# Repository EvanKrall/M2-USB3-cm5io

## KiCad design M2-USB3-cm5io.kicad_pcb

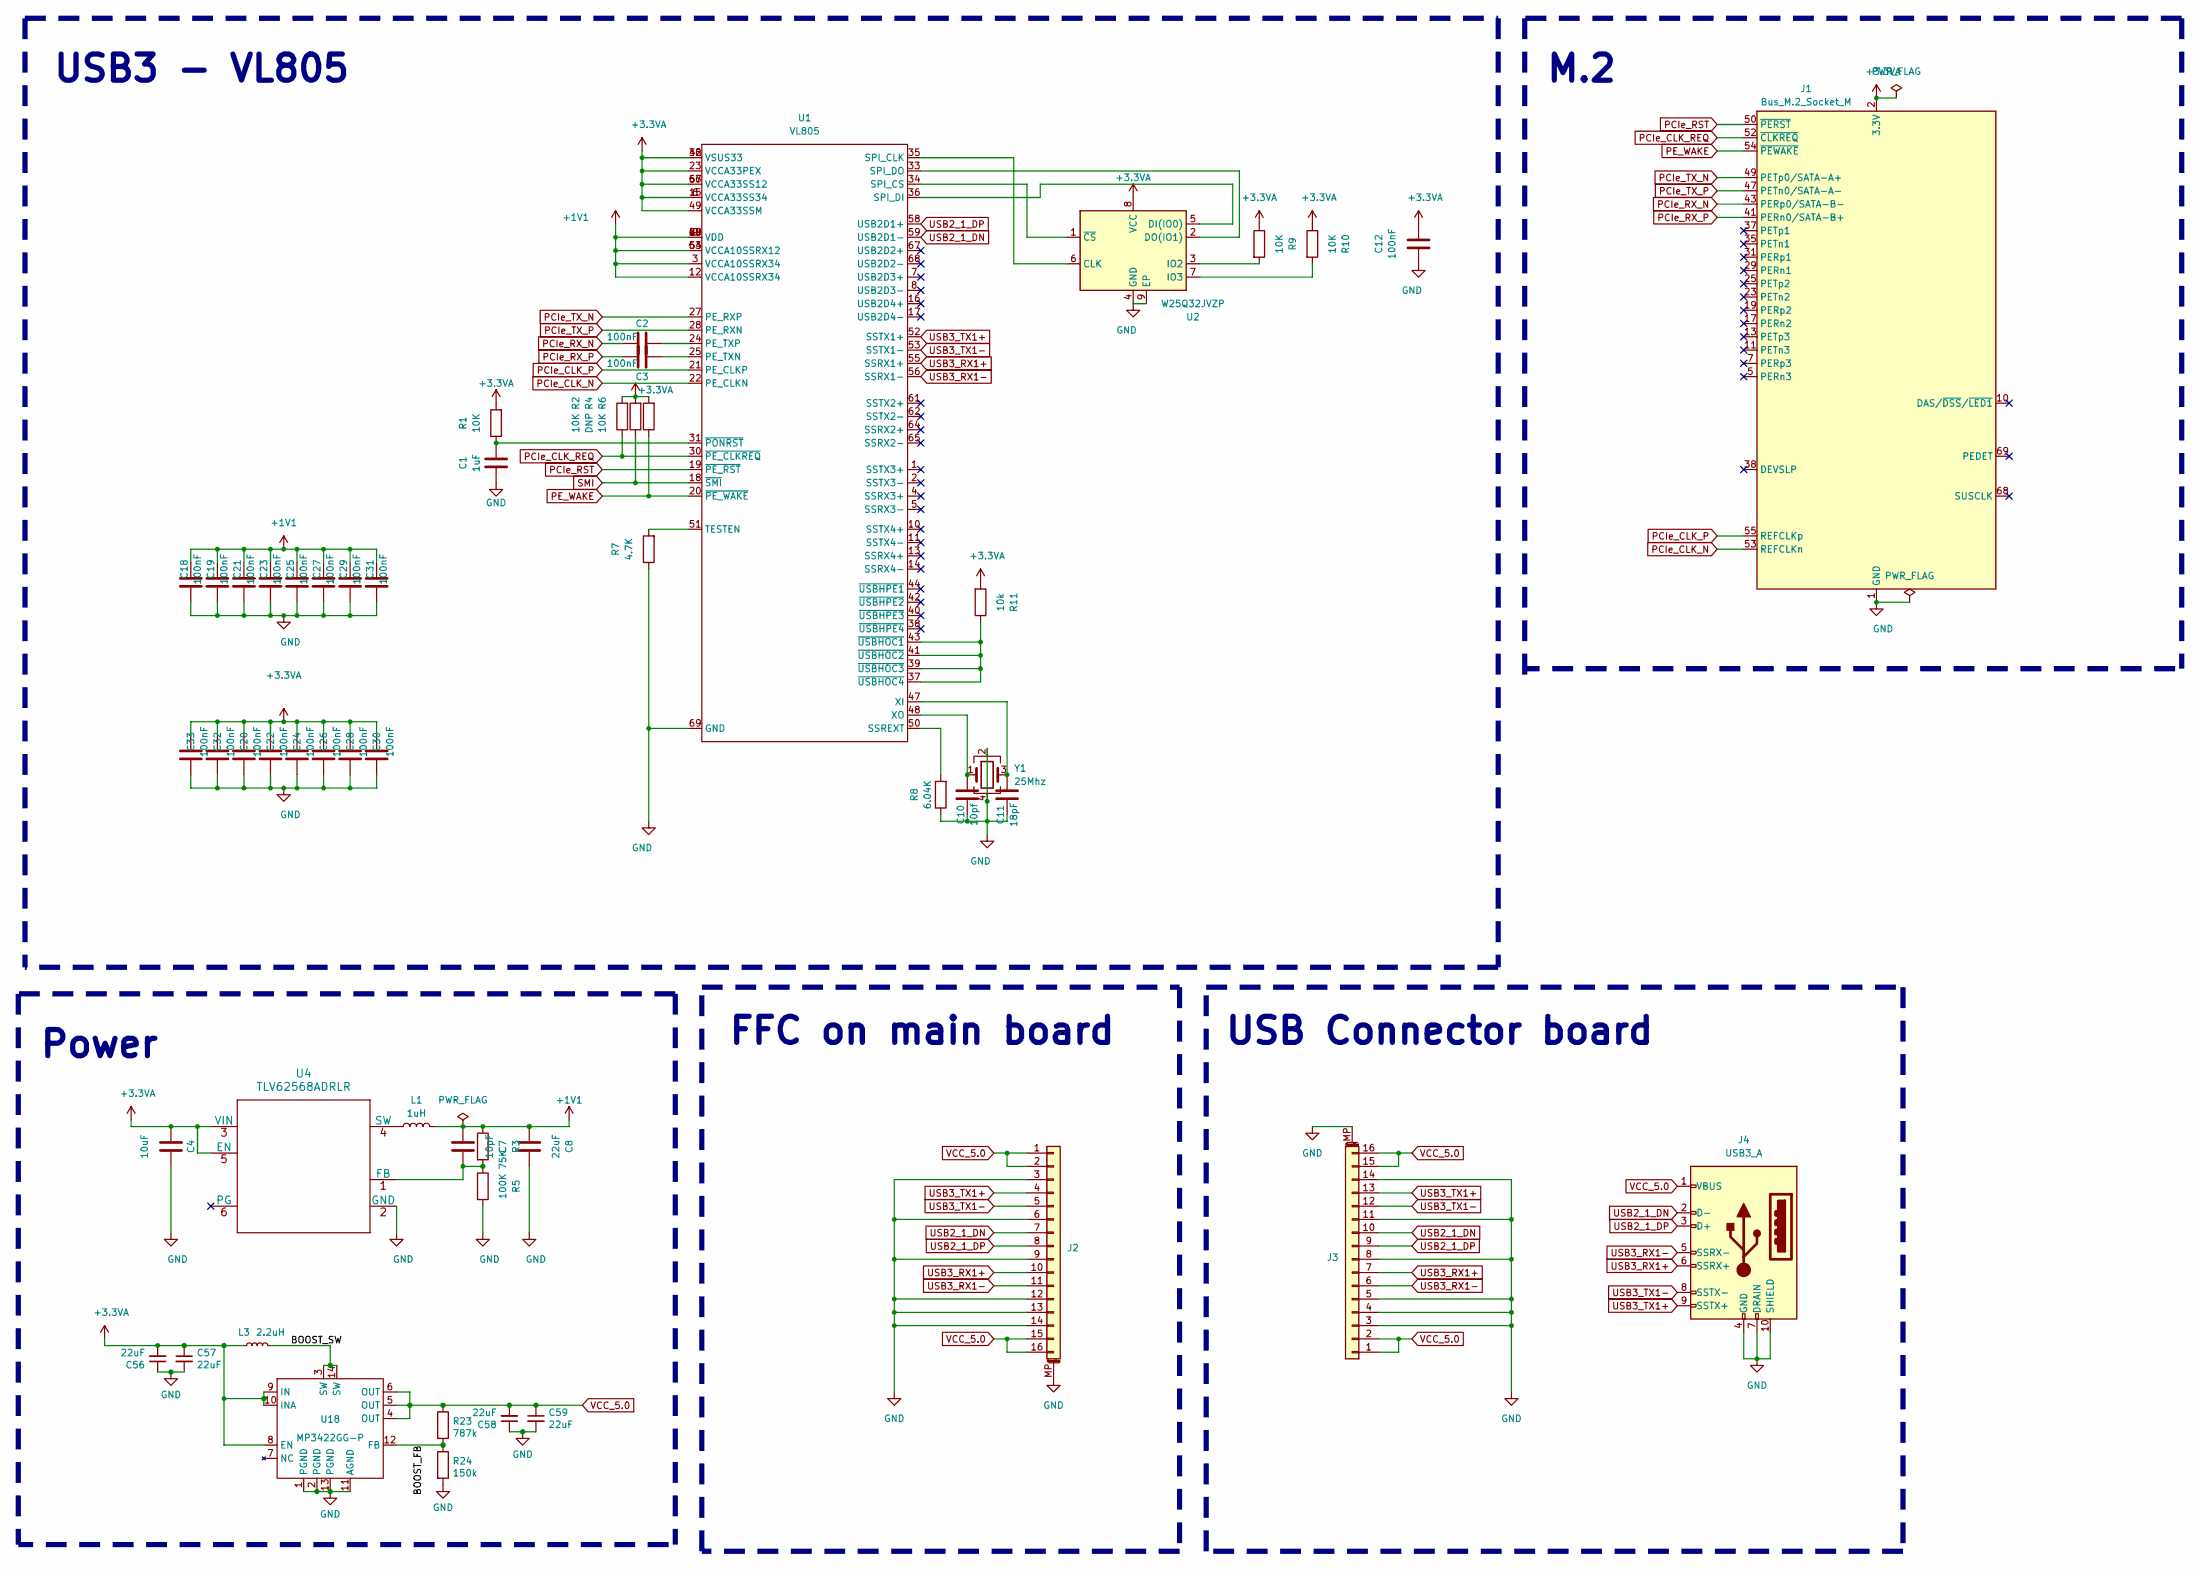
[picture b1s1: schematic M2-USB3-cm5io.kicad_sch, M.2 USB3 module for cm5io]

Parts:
C1: 1uF; C_0402_1005Metric
C2, C3, C12, C18, C19, C20, C21, C22, C23, C24, C25, C26, C27, C28, C29, C30, C31, C32, C33: 100nF; C_0402_1005Metric
C4: 10uF; C_0805_2012Metric
C7: 10pF; C_0402_1005Metric
C8: 22uF; C_0603_1608Metric
C10: 10pf; C_0402_1005Metric
C11: 18pF; C_0402_1005Metric
C56, C57, C58, C59: 22uF; C_0805_2012Metric; Mfg PN CL21A226MQQNNNG‎
J1: Bus_M.2_Socket_M; NGFF_M
J2, J3: Conn_01x16_MountingPin; CF31161D0R0-05-NH
J4: USB3_A; USB-A3-S-RA
L1: 1uH; L_1008_2520Metric
L3: 2.2uH; L_1008_2520Metric; Mfg PN BDHE002520122R2MQ1; Digi-Key PN 2184-BDHE002520122R2MQ1CT-ND
R1, R2, R6, R9, R10: 10K; R_0402_1005Metric
R3: 75K; R_0402_1005Metric
R4: DNP; R_0402_1005Metric
R5: 100K; R_0402_1005Metric
R7: 4.7K; R_0402_1005Metric
R8: 6.04K; R_0402_1005Metric
R11: 10k; R_0402_1005Metric
R23: 787k; R_0402_1005Metric
R24: 150k; R_0402_1005Metric
U1: VL805; QFN-68-1EP_8x8mm_P0.4mm_EP5.2x5.2mm
U2: W25Q32JVZP; DFN-8-1EP_3x2mm_P0.5mm_EP1.36x1.46mm
U4: TLV62568ADRLR; SOT-563
U18: MP3422GG-P
Y1: 25Mhz; Crystal_SMD_3225-4Pin_3.2x2.5mm

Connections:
+1V1: C7.1, C8.1, C18.2, C19.2, C21.2, C23.2, C25.2, C27.2, C29.2, C31.2, L1.2, R3.1, U1.3 (VCCA10SSRX34), U1.9 (VDD), U1.12 (VCCA10SSRX34), U1.29 (VDD), U1.45 (VDD), U1.54 (VCCA10SSRX12), U1.60 (VDD), U1.63 (VCCA10SSRX12)
+3.3VA: C4.2, C12.2, C20.2, C22.2, C24.2, C26.2, C28.2, C30.2, C32.2, C33.2, C56.2, C57.1, J1.2 (3.3V), J1.4 (3.3V), J1.12 (3.3V), J1.14 (3.3V), J1.16 (3.3V), J1.18 (3.3V), J1.70 (3.3V), J1.72 (3.3V), J1.74 (3.3V), L3.1, R1.2, R2.2, R4.2, R6.2, R9.1, R10.1, R11.2, U1.6 (VCCA33SS34), U1.15 (VCCA33SS34), U1.23 (VCCA33PEX), U1.32 (VSUS33), U1.46 (VSUS33), U1.49 (VCCA33SSM), U1.57 (VCCA33SS12), U1.66 (VCCA33SS12), U2.8 (VCC), U4.3 (VIN), U4.5 (EN), U18.8 (EN), U18.9 (IN), U18.10 (INA)
/BOOST_FB: R23.2, R24.1, U18.12 (FB)
/BOOST_SW: L3.2, U18.3 (SW), U18.14 (SW)
GND: C1.1, C4.1, C8.2, C10.1, C11.1, C12.1, C18.1, C19.1, C20.1, C21.1, C22.1, C23.1, C24.1, C25.1, C26.1, C27.1, C28.1, C29.1, C30.1, C31.1, C32.1, C33.1, C56.1, C57.2, C58.1, C59.2, J1.1 (GND), J1.3 (GND), J1.9 (GND), J1.15 (GND), J1.21 (GND), J1.27 (GND), J1.33 (GND), J1.39 (GND), J1.45 (GND), J1.51 (GND), J1.57 (GND), J1.71 (GND), J1.73 (GND), J1.75 (GND), J2.3, J2.6, J2.9, J2.12, J2.13, J2.14, J2.MP (MountPin), J3.3, J3.4, J3.5, J3.8, J3.11, J3.14, J3.MP (MountPin), J4.4 (GND), J4.7 (DRAIN), J4.10 (SHIELD), R5.2, R7.1, R8.1, R24.2, U1.69 (GND), U2.4 (GND), U2.9 (EP), U4.2 (GND), U18.1 (PGND), U18.2 (PGND), U18.11 (AGND), U18.13 (PGND), Y1.2, Y1.4
unnamed: C3.2, U1.25 (PE_TXN)
unnamed: C2.2, U1.24 (PE_TXP)
unnamed: U1.35 (SPI_CLK), U2.6 (CLK)
unnamed: U1.34 (SPI_CS), U2.1 (~CS)
unnamed: U1.36 (SPI_DI), U2.5 (DI(IO0))
unnamed: U1.33 (SPI_DO), U2.2 (DO(IO1))
unnamed: R8.2, U1.50 (SSREXT)
unnamed: R7.2, U1.51 (TESTEN)
unnamed: C11.2, U1.47 (XI), Y1.3
unnamed: C10.2, U1.48 (XO), Y1.1
unnamed: C1.2, R1.1, U1.31 (~PONRST)
unnamed: R11.1, U1.37 (~USBHOC4), U1.39 (~USBHOC3), U1.41 (~USBHOC2), U1.43 (~USBHOC1)
unnamed: R9.2, U2.3 (IO2)
unnamed: R10.2, U2.7 (IO3)
unnamed: C7.2, R3.2, R5.1, U4.1 (FB)
unnamed: L1.1, U4.4 (SW)
PCIe_CLK_N: J1.53 (REFCLKn), U1.22 (PE_CLKN)
PCIe_CLK_P: J1.55 (REFCLKp), U1.21 (PE_CLKP)
PCIe_CLK_REQ: J1.52 (~CLKREQ), R2.1, U1.30 (~PE_CLKREQ)
PCIe_RST: J1.50 (~PERST), U1.19 (~PE_RST)
PCIe_RX_N: C2.1, J1.43 (PERp0/SATA-B-)
PCIe_RX_P: C3.1, J1.41 (PERn0/SATA-B+)
PCIe_TX_N: J1.49 (PETp0/SATA-A+), U1.27 (PE_RXP)
PCIe_TX_P: J1.47 (PETn0/SATA-A-), U1.28 (PE_RXN)
PE_WAKE: J1.54 (~PEWAKE), R6.1, U1.20 (~PE_WAKE)
SMI: R4.1, U1.18 (~SMI)
USB2_1_DN: J2.7, J3.10, J4.2 (D-), U1.59 (USB2D1-)
USB2_1_DP: J2.8, J3.9, J4.3 (D+), U1.58 (USB2D1+)
USB3_RX1+: J2.10, J3.7, J4.6 (SSRX+), U1.55 (SSRX1+)
USB3_RX1-: J2.11, J3.6, J4.5 (SSRX-), U1.56 (SSRX1-)
USB3_TX1+: J2.4, J3.13, J4.9 (SSTX+), U1.52 (SSTX1+)
USB3_TX1-: J2.5, J3.12, J4.8 (SSTX-), U1.53 (SSTX1-)
VCC_5.0: C58.2, C59.1, J2.1, J2.2, J2.15, J2.16, J3.1, J3.2, J3.15, J3.16, J4.1 (VBUS), R23.1, U18.4 (OUT), U18.5 (OUT), U18.6 (OUT)

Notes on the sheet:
Power
M.2
USB3 - VL805
USB Connector board
FFC on main board

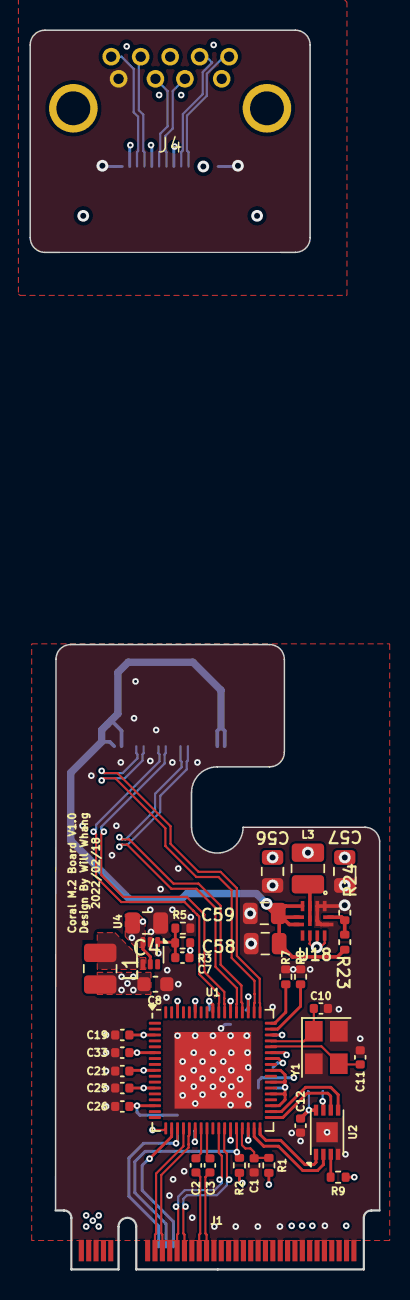
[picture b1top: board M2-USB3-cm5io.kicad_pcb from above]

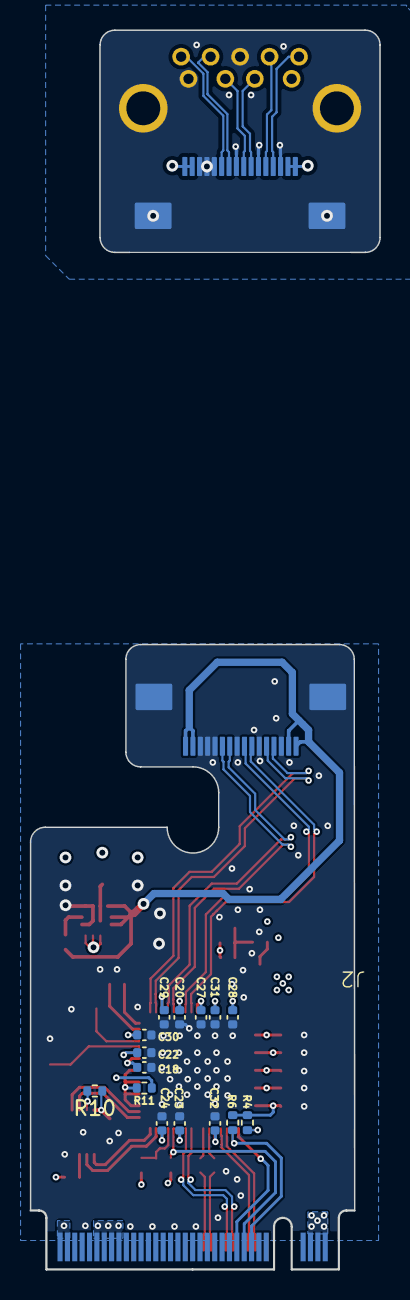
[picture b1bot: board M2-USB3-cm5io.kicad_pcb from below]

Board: 4 copper layers, 22.0 x 42.4 mm, 53 parts (17 on the bottom side), 38 nets.

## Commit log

2026-03-17 Initial commit, copied from https://github.com/will127534/Coral-USB3-M2-Module, delete coral module, add FFC, USB connectors, 5v boost converter
2026-03-17 Fix most ERC/DRC errors
2026-03-17 tweak fills
2026-03-19 Change some components to things I already have in stock
